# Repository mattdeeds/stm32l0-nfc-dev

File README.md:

# `STM32L0 Based Dynamic NFC Tag in Rust`

> Uses [rust-stm32l010f4px-template](https://github.com/mattdeeds/rust-stm32l010f4px-template)

## WIP

Test program blinks LED based off of readings from TMP102 temp sensor.

Currently working on ST25DV integration.

Hardware folder contains Eagle schematic/board files and finished board images.

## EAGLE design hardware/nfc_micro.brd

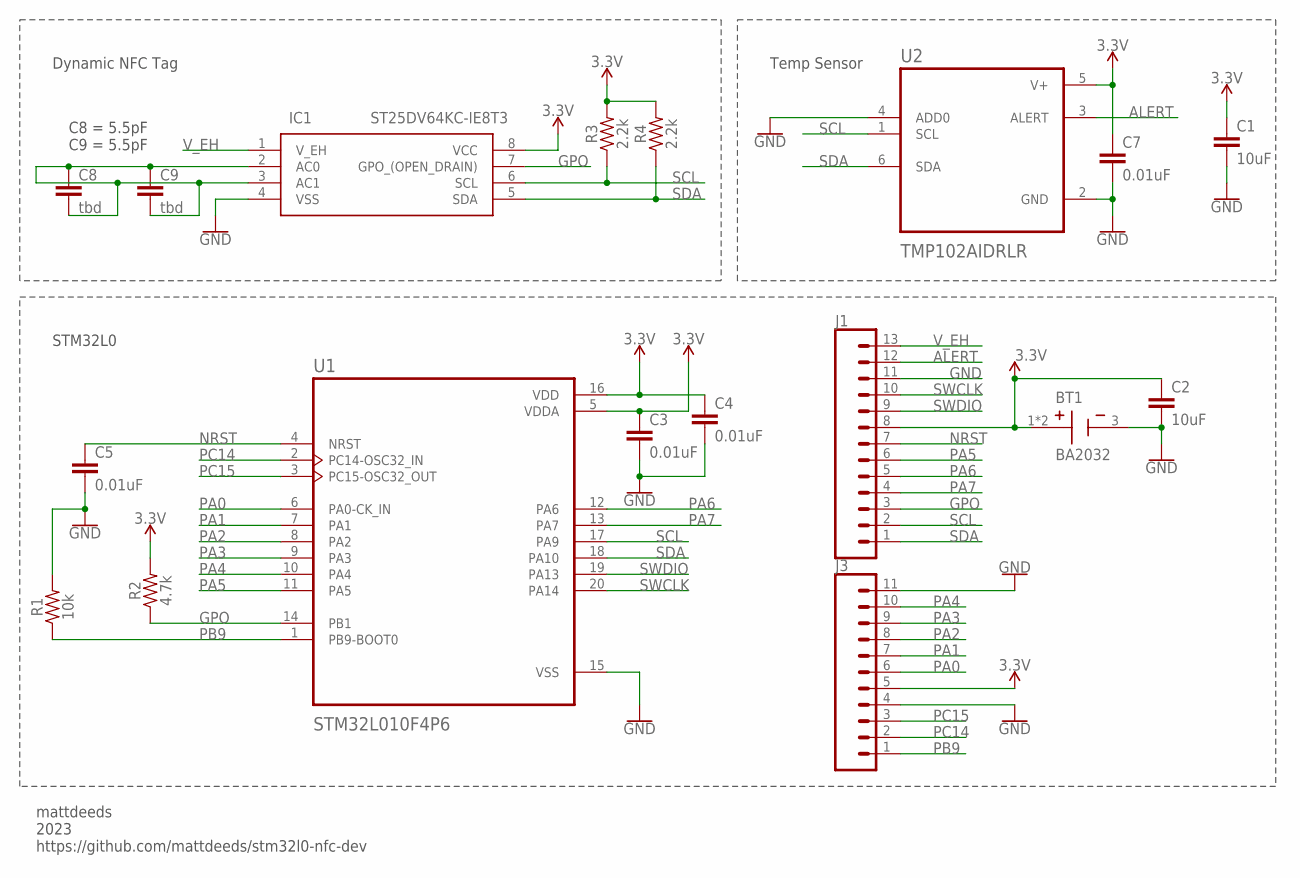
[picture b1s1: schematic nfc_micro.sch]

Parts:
BT1: BA2032; BAT_BA2032
C1, C2: 10uF; 0603
C3, C4, C5, C7: 0.01uF; 0603
C8, C9: tbd; 0603
IC1: ST25DV64KC-IE8T3; SOP65P640X120-8N
J1: CONN_13; 1X13
J3: CONN_11; 1X11
R1: 10k; 0603
R2: 4.7k; 0603
R3, R4: 2.2k; 0603
U1: STM32L010F4P6; SOP65P640X120-20N
U2: TMP102AIDRLR; SOT50P160X60-6N

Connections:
3.3V: BT1.1 (+), BT1.2 (+), C1.1, C2.1, C3.1, C4.1, C7.1, IC1.8 (VCC), J1.8, J3.5, R2.2, R3.2, R4.2, U1.5 (VDDA), U1.16 (VDD), U2.5 (V+)
ALERT: J1.12, U2.3 (ALERT)
GND: BT1.3 (-), C1.2, C2.2, C3.2, C4.2, C5.2, C7.2, IC1.4 (VSS), J1.11, J3.4, J3.11, R1.2, U1.15 (VSS), U2.2 (GND), U2.4 (ADD0)
GPO: IC1.7 (GPO_(OPEN_DRAIN)), J1.3, R2.1, U1.14 (PB1)
unnamed: C8.1, C8.2, C9.1, C9.2, IC1.2 (AC0), IC1.3 (AC1)
NRST: C5.1, J1.7, U1.4 (NRST)
PA0: J3.6, U1.6 (PA0-CK_IN)
PA1: J3.7, U1.7 (PA1)
PA2: J3.8, U1.8 (PA2)
PA3: J3.9, U1.9 (PA3)
PA4: J3.10, U1.10 (PA4)
PA5: J1.6, U1.11 (PA5)
PA6: J1.5, U1.12 (PA6)
PA7: J1.4, U1.13 (PA7)
PB9: J3.1, R1.1, U1.1 (PB9-BOOT0)
PC14: J3.2, U1.2 (PC14-OSC32_IN)
PC15: J3.3, U1.3 (PC15-OSC32_OUT)
SCL: IC1.6 (SCL), J1.2, R3.1, U1.17 (PA9), U2.1 (SCL)
SDA: IC1.5 (SDA), J1.1, R4.1, U1.18 (PA10), U2.6 (SDA)
SWCLK: J1.10, U1.20 (PA14)
SWDIO: J1.9, U1.19 (PA13)
V_EH: IC1.1 (V_EH), J1.13

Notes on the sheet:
Temp Sensor
Dynamic NFC Tag
STM32L0
C8 = 5.5pF C9 = 5.5pF
mattdeeds 2023 https://github.com/mattdeeds/stm32l0-nfc-dev

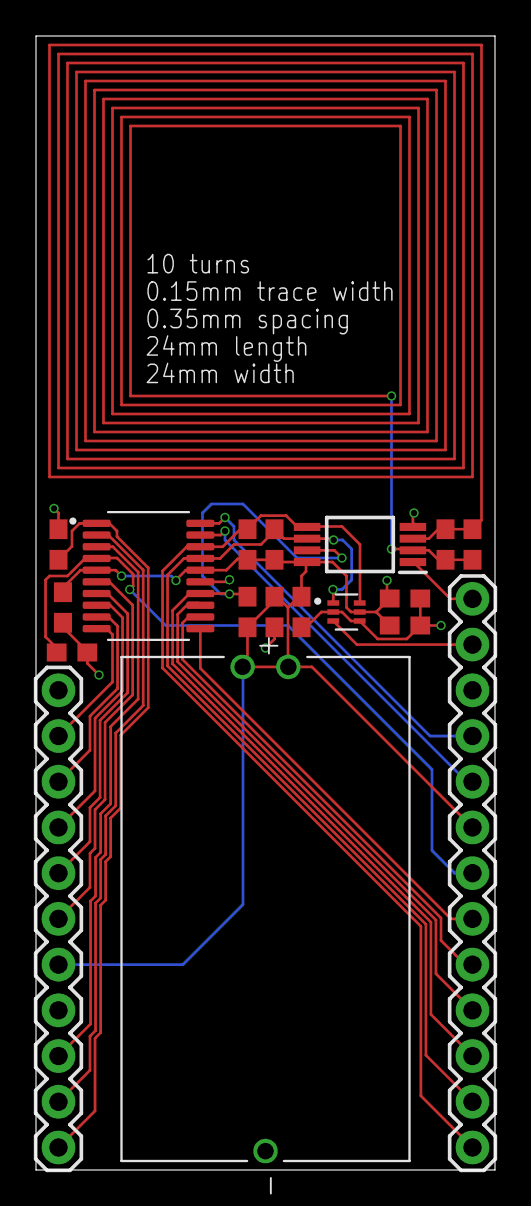
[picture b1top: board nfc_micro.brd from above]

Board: 2 copper layers, 25.5 x 63.0 mm, 18 parts (0 on the bottom side), 22 nets.

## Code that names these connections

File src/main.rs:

#![deny(warnings)]
#![deny(unsafe_code)]
#![no_main]
#![no_std]

extern crate panic_halt;

use cortex_m::asm::delay;
use cortex_m_rt::entry;
use stm32l0xx_hal::{pac, prelude::*, rcc::Config};
use tmp1x2::{Tmp1x2, SlaveAddr};
use embedded_time::rate::*;

#[entry]
fn main() -> ! {
    let dp = pac::Peripherals::take().unwrap();

    // Configure the clock.
    let mut rcc = dp.RCC.freeze(Config::hsi16());

    // Acquire the GPIOA peripheral. This also enables the clock for GPIOA in
    // the RCC register.
    let gpioa = dp.GPIOA.split(&mut rcc);

    // Configure PA1 as output for led
    let mut led = gpioa.pa7.into_push_pull_output();

    // configure I2C pins
    let sda = gpioa.pa10.into_open_drain_output();
    let scl = gpioa.pa9.into_open_drain_output();

    let i2c = dp.I2C1.i2c(sda, scl, Hertz(100_000), &mut rcc);
    let address = SlaveAddr::default();
    let mut sensor = Tmp1x2::new(i2c, address);

    loop {
        
        let temperature = sensor.read_temperature().unwrap();
        let delay_time;

        // Set delay time based on temperature
        // if temperature > 22.0 then fast blink else slow blink
        // temp should be over 22.0 in house

        if temperature > 22.0 {
            delay_time = 4000000;
        } else {
            delay_time = 20000000;
        }

        led.set_high().unwrap();
        delay(delay_time);

        led.set_low().unwrap();
        delay(delay_time);
    }
}

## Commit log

2023-02-17 init
    temp sensor working
2023-03-26 add hardware files

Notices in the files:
parts and their libraries:
SparkFun-Resistors: Licensing: Creative Commons ShareAlike 4.0 International - https://creativecommons.org/licenses/by-sa/4.0
